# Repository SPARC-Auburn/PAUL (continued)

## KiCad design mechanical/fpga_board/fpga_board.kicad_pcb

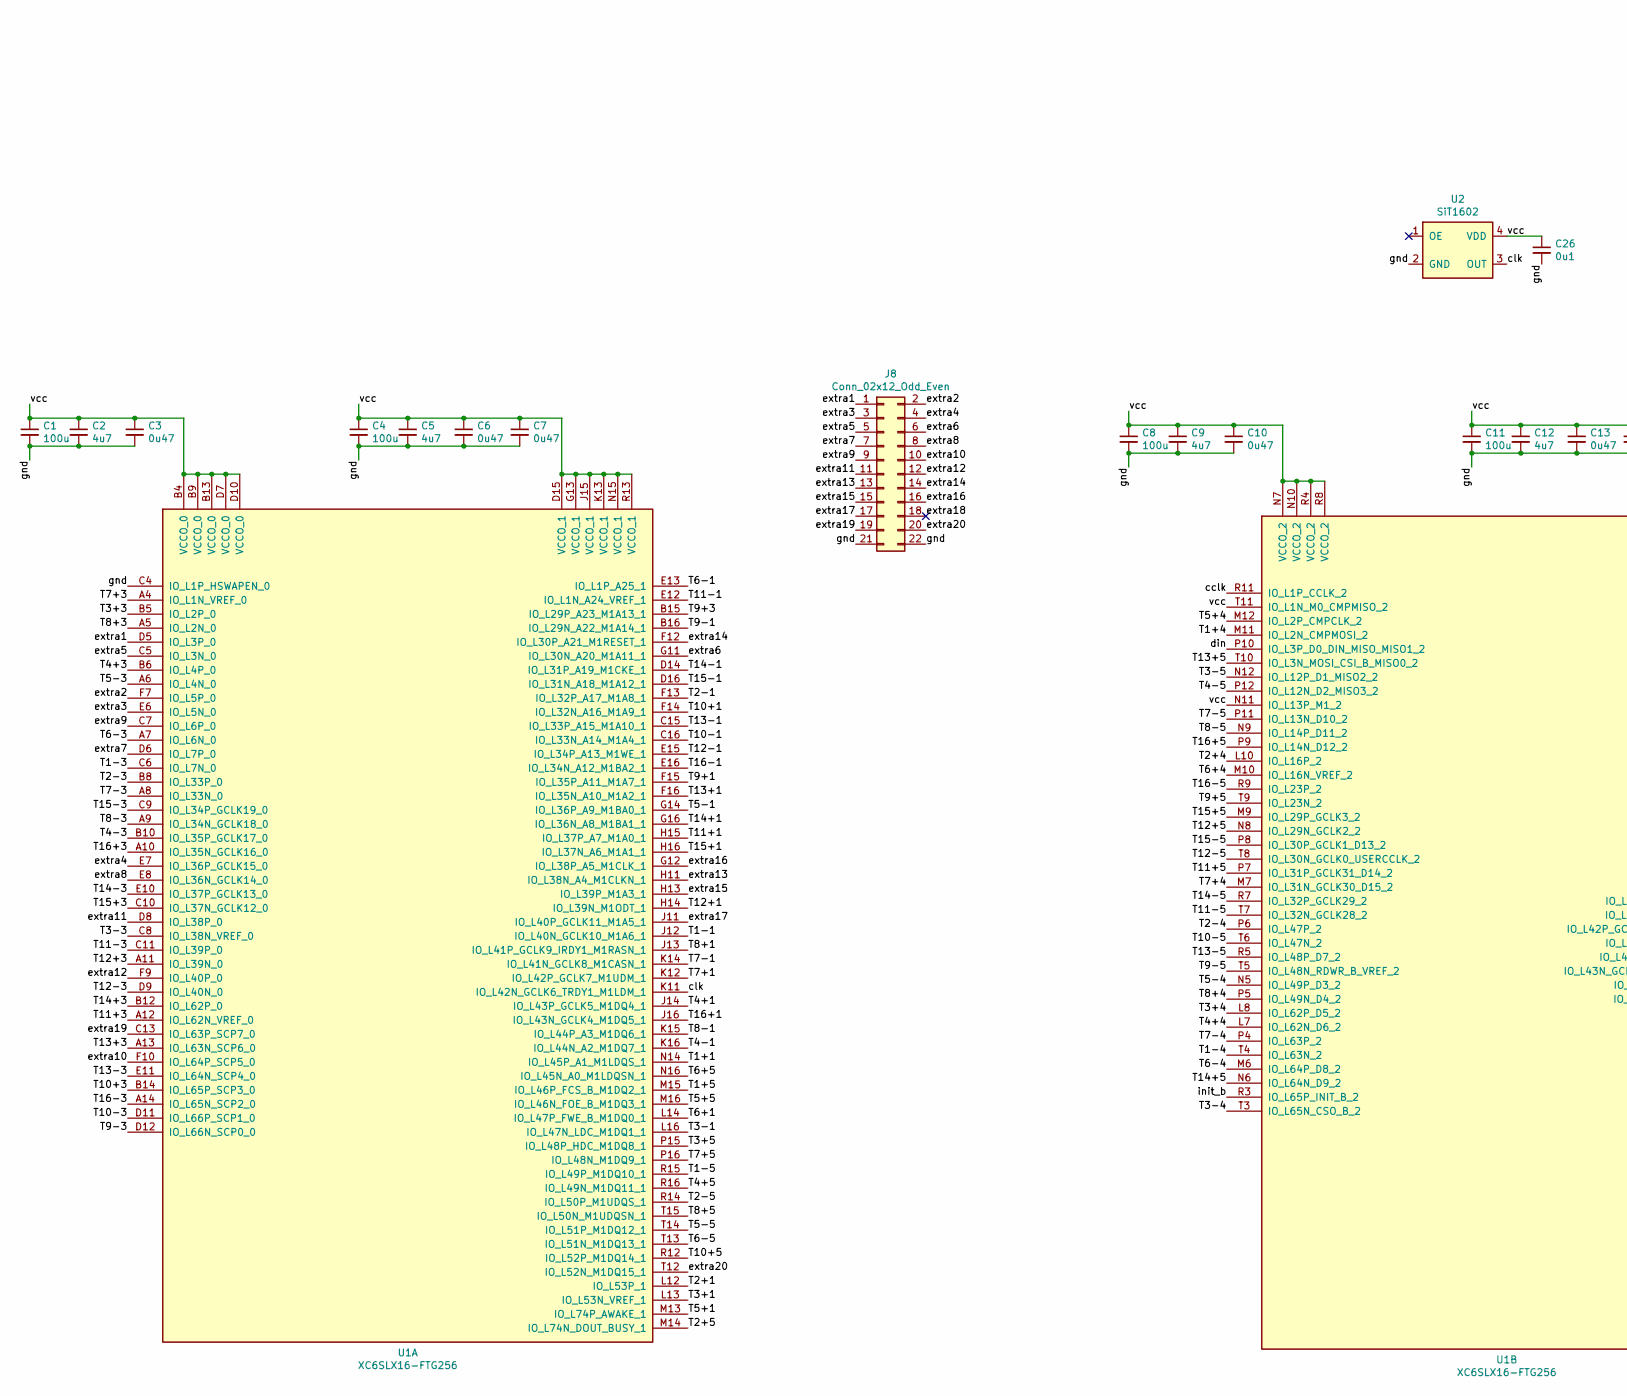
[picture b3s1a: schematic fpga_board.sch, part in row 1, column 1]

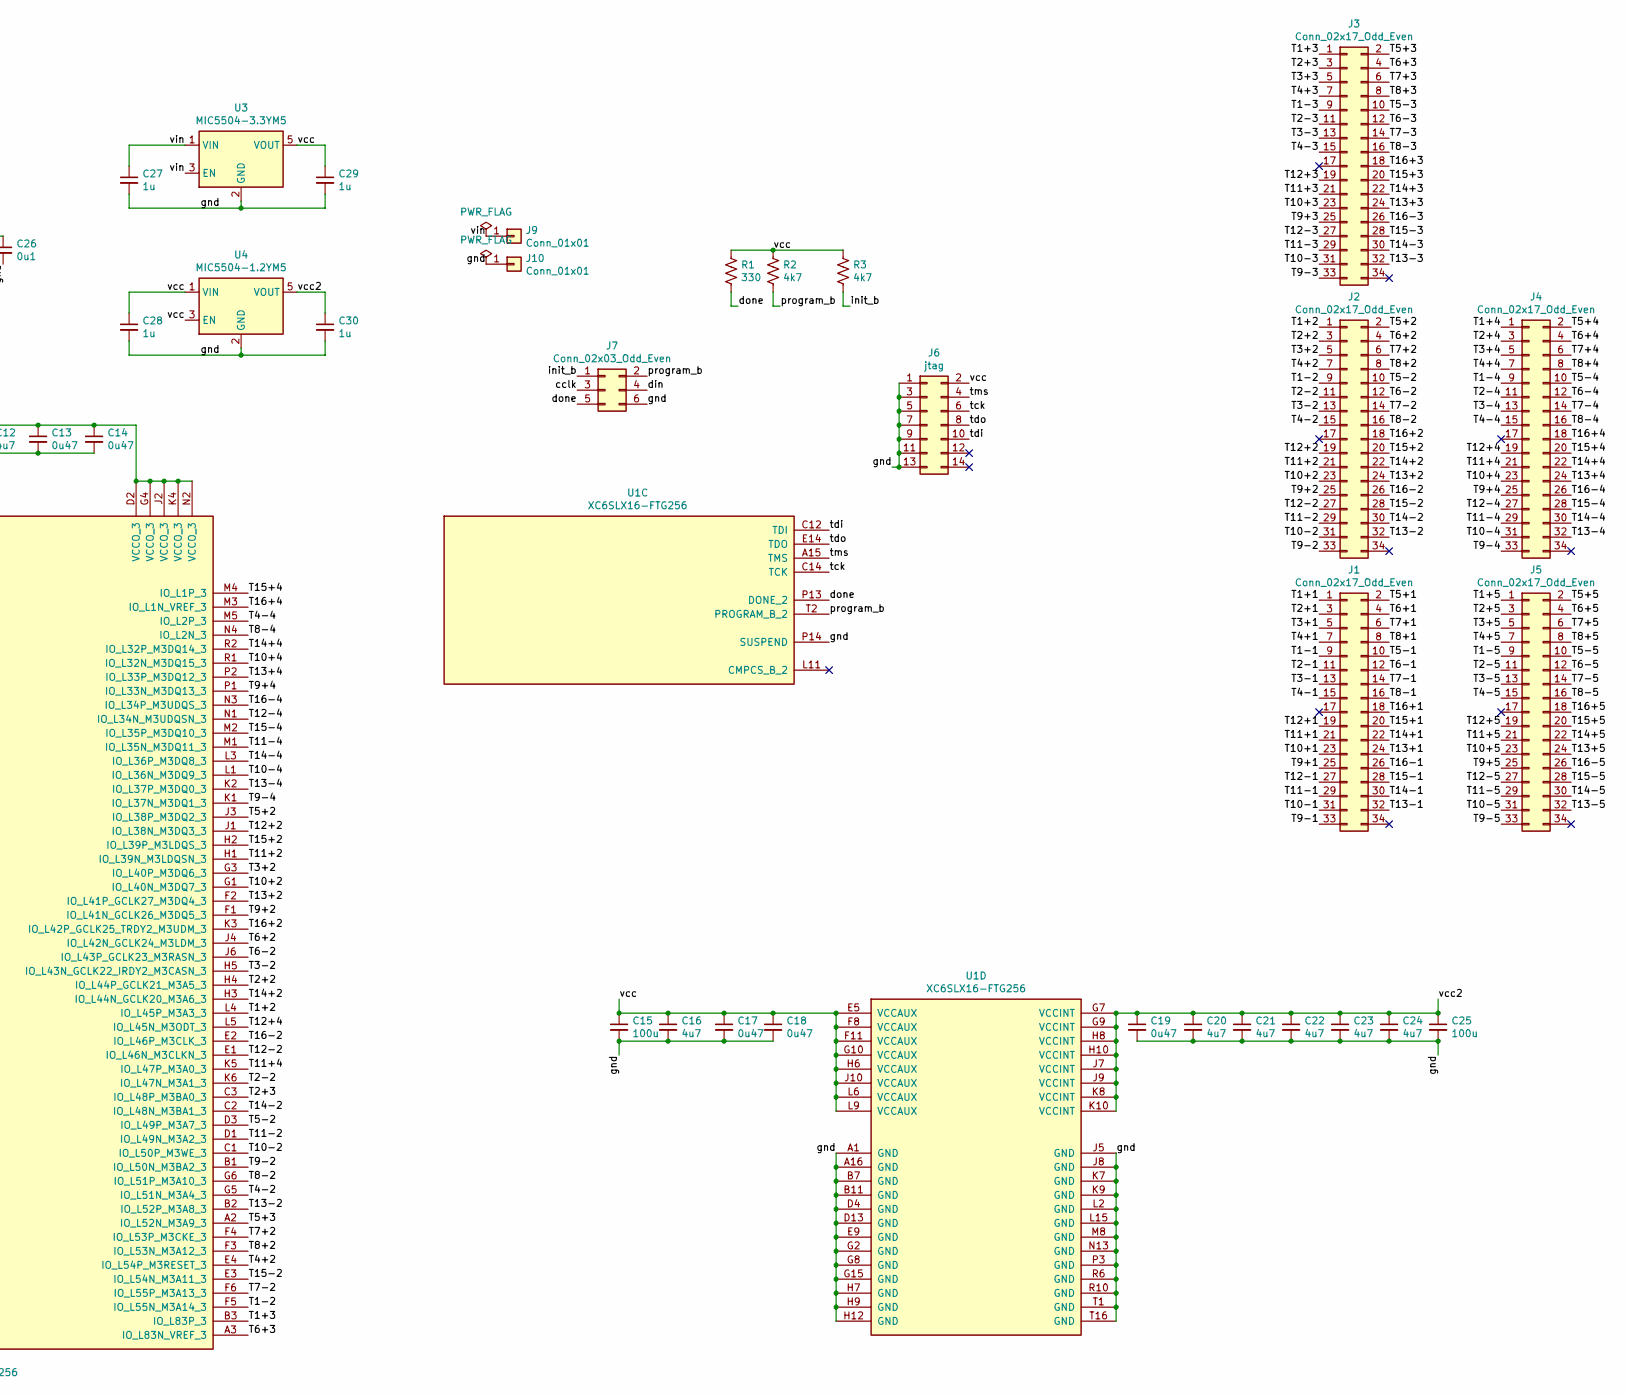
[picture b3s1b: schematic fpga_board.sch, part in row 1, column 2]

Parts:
C1, C4, C8, C11, C15, C25: 100u; C_1210_3225Metric
C2, C5, C9, C12, C16, C20, C21, C22, C23, C24: 4u7; C_0805_2012Metric
C3, C6, C7, C10, C13, C14, C17, C18, C19: 0u47; C_0402_1005Metric
C26: 0u1; C_0402_1005Metric
C27, C28, C29, C30: 1u; C_0603_1608Metric
J1, J2, J3, J4, J5: Conn_02x17_Odd_Even; PinSocket_2x17_P2.54mm_Vertical
J6: jtag; PinSocket_2x07_P2.54mm_Vertical
J7: Conn_02x03_Odd_Even; PinSocket_2x03_P2.54mm_Vertical
J8: Conn_02x12_Odd_Even; PinSocket_2x11_P2.54mm_Vertical
J9, J10: Conn_01x01; Pin_D1.3mm_L11.0mm
R1: 330; R_0603_1608Metric
R2, R3: 4k7; R_0603_1608Metric
U1: XC6SLX16-FTG256; Xilinx_FTG256
U2: SiT1602; SiT1602_7_5
U3: MIC5504-3.3YM5; SOT-23-5
U4: MIC5504-1.2YM5; SOT-23-5

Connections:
/T1+1: J1.1, U1.N14 (IO_L45P_A1_M1LDQS_1)
/T1+2: J2.1, U1.L4 (IO_L45P_M3A3_3)
/T1+3: J3.1, U1.B3 (IO_L83P_3)
/T1+4: J4.1, U1.M11 (IO_L2N_CMPMOSI_2)
/T1+5: J5.1, U1.M15 (IO_L46P_FCS_B_M1DQ2_1)
/T1-1: J1.9, U1.J12 (IO_L40N_GCLK10_M1A6_1)
/T1-2: J2.9, U1.F5 (IO_L55N_M3A14_3)
/T1-3: J3.9, U1.C6 (IO_L7N_0)
/T1-4: J4.9, U1.T4 (IO_L63N_2)
/T1-5: J5.9, U1.R15 (IO_L49P_M1DQ10_1)
/T2+1: J1.3, U1.L12 (IO_L53P_1)
/T2+2: J2.3, U1.H4 (IO_L44P_GCLK21_M3A5_3)
/T2+3: J3.3, U1.C3 (IO_L48P_M3BA0_3)
/T2+4: J4.3, U1.L10 (IO_L16P_2)
/T2+5: J5.3, U1.M14 (IO_L74N_DOUT_BUSY_1)
/T2-1: J1.11, U1.F13 (IO_L32P_A17_M1A8_1)
/T2-2: J2.11, U1.K6 (IO_L47N_M3A1_3)
/T2-3: J3.11, U1.B8 (IO_L33P_0)
/T2-4: J4.11, U1.P6 (IO_L47P_2)
/T2-5: J5.11, U1.R14 (IO_L50P_M1UDQS_1)
/T3+1: J1.5, U1.L13 (IO_L53N_VREF_1)
/T3+2: J2.5, U1.G3 (IO_L40P_M3DQ6_3)
/T3+3: J3.5, U1.B5 (IO_L2P_0)
/T3+4: J4.5, U1.L8 (IO_L62P_D5_2)
/T3+5: J5.5, U1.P15 (IO_L48P_HDC_M1DQ8_1)
/T3-1: J1.13, U1.L16 (IO_L47N_LDC_M1DQ1_1)
/T3-2: J2.13, U1.H5 (IO_L43N_GCLK22_IRDY2_M3CASN_3)
/T3-3: J3.13, U1.C8 (IO_L38N_VREF_0)
/T3-4: J4.13, U1.T3 (IO_L65N_CSO_B_2)
/T3-5: J5.13, U1.N12 (IO_L12P_D1_MISO2_2)
/T4+1: J1.7, U1.J14 (IO_L43P_GCLK5_M1DQ4_1)
/T4+2: J2.7, U1.E4 (IO_L54P_M3RESET_3)
/T4+3: J3.7, U1.B6 (IO_L4P_0)
/T4+4: J4.7, U1.L7 (IO_L62N_D6_2)
/T4+5: J5.7, U1.R16 (IO_L49N_M1DQ11_1)
/T4-1: J1.15, U1.K16 (IO_L44N_A2_M1DQ7_1)
/T4-2: J2.15, U1.G5 (IO_L51N_M3A4_3)
/T4-3: J3.15, U1.B10 (IO_L35P_GCLK17_0)
/T4-4: J4.15, U1.M5 (IO_L2P_3)
/T4-5: J5.15, U1.P12 (IO_L12N_D2_MISO3_2)
/T5+1: J1.2, U1.M13 (IO_L74P_AWAKE_1)
/T5+2: J2.2, U1.J3 (IO_L38P_M3DQ2_3)
/T5+3: J3.2, U1.A2 (IO_L52N_M3A9_3)
/T5+4: J4.2, U1.M12 (IO_L2P_CMPCLK_2)
/T5+5: J5.2, U1.M16 (IO_L46N_FOE_B_M1DQ3_1)
/T5-1: J1.10, U1.G14 (IO_L36P_A9_M1BA0_1)
/T5-2: J2.10, U1.D3 (IO_L49P_M3A7_3)
/T5-3: J3.10, U1.A6 (IO_L4N_0)
/T5-4: J4.10, U1.N5 (IO_L49P_D3_2)
/T5-5: J5.10, U1.T14 (IO_L51P_M1DQ12_1)
/T6+1: J1.4, U1.L14 (IO_L47P_FWE_B_M1DQ0_1)
/T6+2: J2.4, U1.J4 (IO_L42N_GCLK24_M3LDM_3)
/T6+3: J3.4, U1.A3 (IO_L83N_VREF_3)
/T6+4: J4.4, U1.M10 (IO_L16N_VREF_2)
/T6+5: J5.4, U1.N16 (IO_L45N_A0_M1LDQSN_1)
/T6-1: J1.12, U1.E13 (IO_L1P_A25_1)
/T6-2: J2.12, U1.J6 (IO_L43P_GCLK23_M3RASN_3)
/T6-3: J3.12, U1.A7 (IO_L6N_0)
/T6-4: J4.12, U1.M6 (IO_L64P_D8_2)
/T6-5: J5.12, U1.T13 (IO_L51N_M1DQ13_1)
/T7+1: J1.6, U1.K12 (IO_L42P_GCLK7_M1UDM_1)
/T7+2: J2.6, U1.F4 (IO_L53P_M3CKE_3)
/T7+3: J3.6, U1.A4 (IO_L1N_VREF_0)
/T7+4: J4.6, U1.M7 (IO_L31N_GCLK30_D15_2)
/T7+5: J5.6, U1.P16 (IO_L48N_M1DQ9_1)
/T7-1: J1.14, U1.K14 (IO_L41N_GCLK8_M1CASN_1)
/T7-2: J2.14, U1.F6 (IO_L55P_M3A13_3)
/T7-3: J3.14, U1.A8 (IO_L33N_0)
/T7-4: J4.14, U1.P4 (IO_L63P_2)
/T7-5: J5.14, U1.P11 (IO_L13N_D10_2)
/T8+1: J1.8, U1.J13 (IO_L41P_GCLK9_IRDY1_M1RASN_1)
/T8+2: J2.8, U1.F3 (IO_L53N_M3A12_3)
/T8+3: J3.8, U1.A5 (IO_L2N_0)
/T8+4: J4.8, U1.P5 (IO_L49N_D4_2)
/T8+5: J5.8, U1.T15 (IO_L50N_M1UDQSN_1)
/T8-1: J1.16, U1.K15 (IO_L44P_A3_M1DQ6_1)
/T8-2: J2.16, U1.G6 (IO_L51P_M3A10_3)
/T8-3: J3.16, U1.A9 (IO_L34N_GCLK18_0)
/T8-4: J4.16, U1.N4 (IO_L2N_3)
/T8-5: J5.16, U1.N9 (IO_L14P_D11_2)
/T9+1: J1.25, U1.F15 (IO_L35P_A11_M1A7_1)
/T9+2: J2.25, U1.F1 (IO_L41N_GCLK26_M3DQ5_3)
/T9+3: J3.25, U1.B15 (IO_L29P_A23_M1A13_1)
/T9+4: J4.25, U1.P1 (IO_L33N_M3DQ13_3)
/T9+5: J5.25, U1.T9 (IO_L23N_2)
/T9-1: J1.33, U1.B16 (IO_L29N_A22_M1A14_1)
/T9-2: J2.33, U1.B1 (IO_L50N_M3BA2_3)
/T9-3: J3.33, U1.D12 (IO_L66N_SCP0_0)
/T9-4: J4.33, U1.K1 (IO_L37N_M3DQ1_3)
/T9-5: J5.33, U1.T5 (IO_L48N_RDWR_B_VREF_2)
/T10+1: J1.23, U1.F14 (IO_L32N_A16_M1A9_1)
/T10+2: J2.23, U1.G1 (IO_L40N_M3DQ7_3)
/T10+3: J3.23, U1.B14 (IO_L65P_SCP3_0)
/T10+4: J4.23, U1.R1 (IO_L32N_M3DQ15_3)
/T10+5: J5.23, U1.R12 (IO_L52P_M1DQ14_1)
/T10-1: J1.31, U1.C16 (IO_L33N_A14_M1A4_1)
/T10-2: J2.31, U1.C1 (IO_L50P_M3WE_3)
/T10-3: J3.31, U1.D11 (IO_L66P_SCP1_0)
/T10-4: J4.31, U1.L1 (IO_L36N_M3DQ9_3)
/T10-5: J5.31, U1.T6 (IO_L47N_2)
/T11+1: J1.21, U1.H15 (IO_L37P_A7_M1A0_1)
/T11+2: J2.21, U1.H1 (IO_L39N_M3LDQSN_3)
/T11+3: J3.21, U1.A12 (IO_L62N_VREF_0)
/T11+4: J4.21, U1.K5 (IO_L47P_M3A0_3)
/T11+5: J5.21, U1.P7 (IO_L31P_GCLK31_D14_2)
/T11-1: J1.29, U1.E12 (IO_L1N_A24_VREF_1)
/T11-2: J2.29, U1.D1 (IO_L49N_M3A2_3)
/T11-3: J3.29, U1.C11 (IO_L39P_0)
/T11-4: J4.29, U1.M1 (IO_L35N_M3DQ11_3)
/T11-5: J5.29, U1.T7 (IO_L32N_GCLK28_2)
/T12+1: J1.19, U1.H14 (IO_L39N_M1ODT_1)
/T12+2: J2.19, U1.J1 (IO_L38N_M3DQ3_3)
/T12+3: J3.19, U1.A11 (IO_L39N_0)
/T12+4: J4.19, U1.L5 (IO_L45N_M3ODT_3)
/T12+5: J5.19, U1.N8 (IO_L29N_GCLK2_2)
/T12-1: J1.27, U1.E15 (IO_L34P_A13_M1WE_1)
/T12-2: J2.27, U1.E1 (IO_L46N_M3CLKN_3)
/T12-3: J3.27, U1.D9 (IO_L40N_0)
/T12-4: J4.27, U1.N1 (IO_L34N_M3UDQSN_3)
/T12-5: J5.27, U1.T8 (IO_L30N_GCLK0_USERCCLK_2)
/T13+1: J1.24, U1.F16 (IO_L35N_A10_M1A2_1)
/T13+2: J2.24, U1.F2 (IO_L41P_GCLK27_M3DQ4_3)
/T13+3: J3.24, U1.A13 (IO_L63N_SCP6_0)
/T13+4: J4.24, U1.P2 (IO_L33P_M3DQ12_3)
/T13+5: J5.24, U1.T10 (IO_L3N_MOSI_CSI_B_MISO0_2)
/T13-1: J1.32, U1.C15 (IO_L33P_A15_M1A10_1)
/T13-2: J2.32, U1.B2 (IO_L52P_M3A8_3)
/T13-3: J3.32, U1.E11 (IO_L64N_SCP4_0)
/T13-4: J4.32, U1.K2 (IO_L37P_M3DQ0_3)
/T13-5: J5.32, U1.R5 (IO_L48P_D7_2)
/T14+1: J1.22, U1.G16 (IO_L36N_A8_M1BA1_1)
/T14+2: J2.22, U1.H3 (IO_L44N_GCLK20_M3A6_3)
/T14+3: J3.22, U1.B12 (IO_L62P_0)
/T14+4: J4.22, U1.R2 (IO_L32P_M3DQ14_3)
/T14+5: J5.22, U1.N6 (IO_L64N_D9_2)
/T14-1: J1.30, U1.D14 (IO_L31P_A19_M1CKE_1)
/T14-2: J2.30, U1.C2 (IO_L48N_M3BA1_3)
/T14-3: J3.30, U1.E10 (IO_L37P_GCLK13_0)
/T14-4: J4.30, U1.L3 (IO_L36P_M3DQ8_3)
/T14-5: J5.30, U1.R7 (IO_L32P_GCLK29_2)
/T15+1: J1.20, U1.H16 (IO_L37N_A6_M1A1_1)
/T15+2: J2.20, U1.H2 (IO_L39P_M3LDQS_3)
/T15+3: J3.20, U1.C10 (IO_L37N_GCLK12_0)
/T15+4: J4.20, U1.M4 (IO_L1P_3)
/T15+5: J5.20, U1.M9 (IO_L29P_GCLK3_2)
/T15-1: J1.28, U1.D16 (IO_L31N_A18_M1A12_1)
/T15-2: J2.28, U1.E3 (IO_L54N_M3A11_3)
/T15-3: J3.28, U1.C9 (IO_L34P_GCLK19_0)
/T15-4: J4.28, U1.M2 (IO_L35P_M3DQ10_3)
/T15-5: J5.28, U1.P8 (IO_L30P_GCLK1_D13_2)
/T16+1: J1.18, U1.J16 (IO_L43N_GCLK4_M1DQ5_1)
/T16+2: J2.18, U1.K3 (IO_L42P_GCLK25_TRDY2_M3UDM_3)
/T16+3: J3.18, U1.A10 (IO_L35N_GCLK16_0)
/T16+4: J4.18, U1.M3 (IO_L1N_VREF_3)
/T16+5: J5.18, U1.P9 (IO_L14N_D12_2)
/T16-1: J1.26, U1.E16 (IO_L34N_A12_M1BA2_1)
/T16-2: J2.26, U1.E2 (IO_L46P_M3CLK_3)
/T16-3: J3.26, U1.A14 (IO_L65N_SCP2_0)
/T16-4: J4.26, U1.N3 (IO_L34P_M3UDQS_3)
/T16-5: J5.26, U1.R9 (IO_L23P_2)
/cclk: J7.3, U1.R11 (IO_L1P_CCLK_2)
/clk: U1.K11 (IO_L42N_GCLK6_TRDY1_M1LDM_1), U2.3 (OUT)
/din: J7.4, U1.P10 (IO_L3P_D0_DIN_MISO_MISO1_2)
/done: J7.5, R1.2, U1.P13 (DONE_2)
/extra1: J8.1, U1.D5 (IO_L3P_0)
/extra2: J8.2, U1.F7 (IO_L5P_0)
/extra3: J8.3, U1.E6 (IO_L5N_0)
/extra4: J8.4, U1.E7 (IO_L36P_GCLK15_0)
/extra5: J8.5, U1.C5 (IO_L3N_0)
/extra6: J8.6, U1.G11 (IO_L30N_A20_M1A11_1)
/extra7: J8.7, U1.D6 (IO_L7P_0)
/extra8: J8.8, U1.E8 (IO_L36N_GCLK14_0)
/extra9: J8.9, U1.C7 (IO_L6P_0)
/extra10: J8.10, U1.F10 (IO_L64P_SCP5_0)
/extra11: J8.11, U1.D8 (IO_L38P_0)
/extra12: J8.12, U1.F9 (IO_L40P_0)
/extra13: J8.13, U1.H11 (IO_L38N_A4_M1CLKN_1)
/extra14: J8.14, U1.F12 (IO_L30P_A21_M1RESET_1)
/extra15: J8.15, U1.H13 (IO_L39P_M1A3_1)
/extra16: J8.16, U1.G12 (IO_L38P_A5_M1CLK_1)
/extra17: J8.17, U1.J11 (IO_L40P_GCLK11_M1A5_1)
/extra18: J8.18
/extra19: J8.19, U1.C13 (IO_L63P_SCP7_0)
/extra20: J8.20, U1.T12 (IO_L52N_M1DQ15_1)
/gnd: C1.2, C2.2, C3.2, C4.2, C5.2, C6.2, C7.2, C8.2, C9.2, C10.2, C11.2, C12.2, C13.2, C14.2, C15.2, C16.2, C17.2, C18.2, C19.2, C20.2, C21.2, C22.2, C23.2, C24.2, C25.2, C26.2, C27.2, C28.2, C29.2, C30.2, J6.1, J6.3, J6.5, J6.7, J6.9, J6.11, J6.13, J7.6, J8.21, J8.22, J10.1, U1.A1 (GND), U1.A16 (GND), U1.B7 (GND), U1.B11 (GND), U1.C4 (IO_L1P_HSWAPEN_0), U1.D4 (GND), U1.D13 (GND), U1.E9 (GND), U1.G2 (GND), U1.G8 (GND), U1.G15 (GND), U1.H7 (GND), U1.H9 (GND), U1.H12 (GND), U1.J5 (GND), U1.J8 (GND), U1.K7 (GND), U1.K9 (GND), U1.L2 (GND), U1.L15 (GND), U1.M8 (GND), U1.N13 (GND), U1.P3 (GND), U1.P14 (SUSPEND), U1.R6 (GND), U1.R10 (GND), U1.T1 (GND), U1.T16 (GND), U2.2 (GND), U3.2 (GND), U4.2 (GND)
/init_b: J7.1, R3.2, U1.R3 (IO_L65P_INIT_B_2)
/program_b: J7.2, R2.2, U1.T2 (PROGRAM_B_2)
/tck: J6.6, U1.C14 (TCK)
/tdi: J6.10, U1.C12 (TDI)
/tdo: J6.8, U1.E14 (TDO)
/tms: J6.4, U1.A15 (TMS)
/vcc: C1.1, C2.1, C3.1, C4.1, C5.1, C6.1, C7.1, C8.1, C9.1, C10.1, C11.1, C12.1, C13.1, C14.1, C15.1, C16.1, C17.1, C18.1, C26.1, C28.1, C29.1, J6.2, R1.1, R2.1, R3.1, U1.B4 (VCCO_0), U1.B9 (VCCO_0), U1.B13 (VCCO_0), U1.D2 (VCCO_3), U1.D7 (VCCO_0), U1.D10 (VCCO_0), U1.D15 (VCCO_1), U1.E5 (VCCAUX), U1.F8 (VCCAUX), U1.F11 (VCCAUX), U1.G4 (VCCO_3), U1.G10 (VCCAUX), U1.G13 (VCCO_1), U1.H6 (VCCAUX), U1.J2 (VCCO_3), U1.J10 (VCCAUX), U1.J15 (VCCO_1), U1.K4 (VCCO_3), U1.K13 (VCCO_1), U1.L6 (VCCAUX), U1.L9 (VCCAUX), U1.N2 (VCCO_3), U1.N7 (VCCO_2), U1.N10 (VCCO_2), U1.N11 (IO_L13P_M1_2), U1.N15 (VCCO_1), U1.R4 (VCCO_2), U1.R8 (VCCO_2), U1.R13 (VCCO_1), U1.T11 (IO_L1N_M0_CMPMISO_2), U2.4 (VDD), U3.5 (VOUT), U4.1 (VIN), U4.3 (EN)
/vcc2: C19.1, C20.1, C21.1, C22.1, C23.1, C24.1, C25.1, C30.1, U1.G7 (VCCINT), U1.G9 (VCCINT), U1.H8 (VCCINT), U1.H10 (VCCINT), U1.J7 (VCCINT), U1.J9 (VCCINT), U1.K8 (VCCINT), U1.K10 (VCCINT), U4.5 (VOUT)
/vin: C27.1, J9.1, U3.1 (VIN), U3.3 (EN)

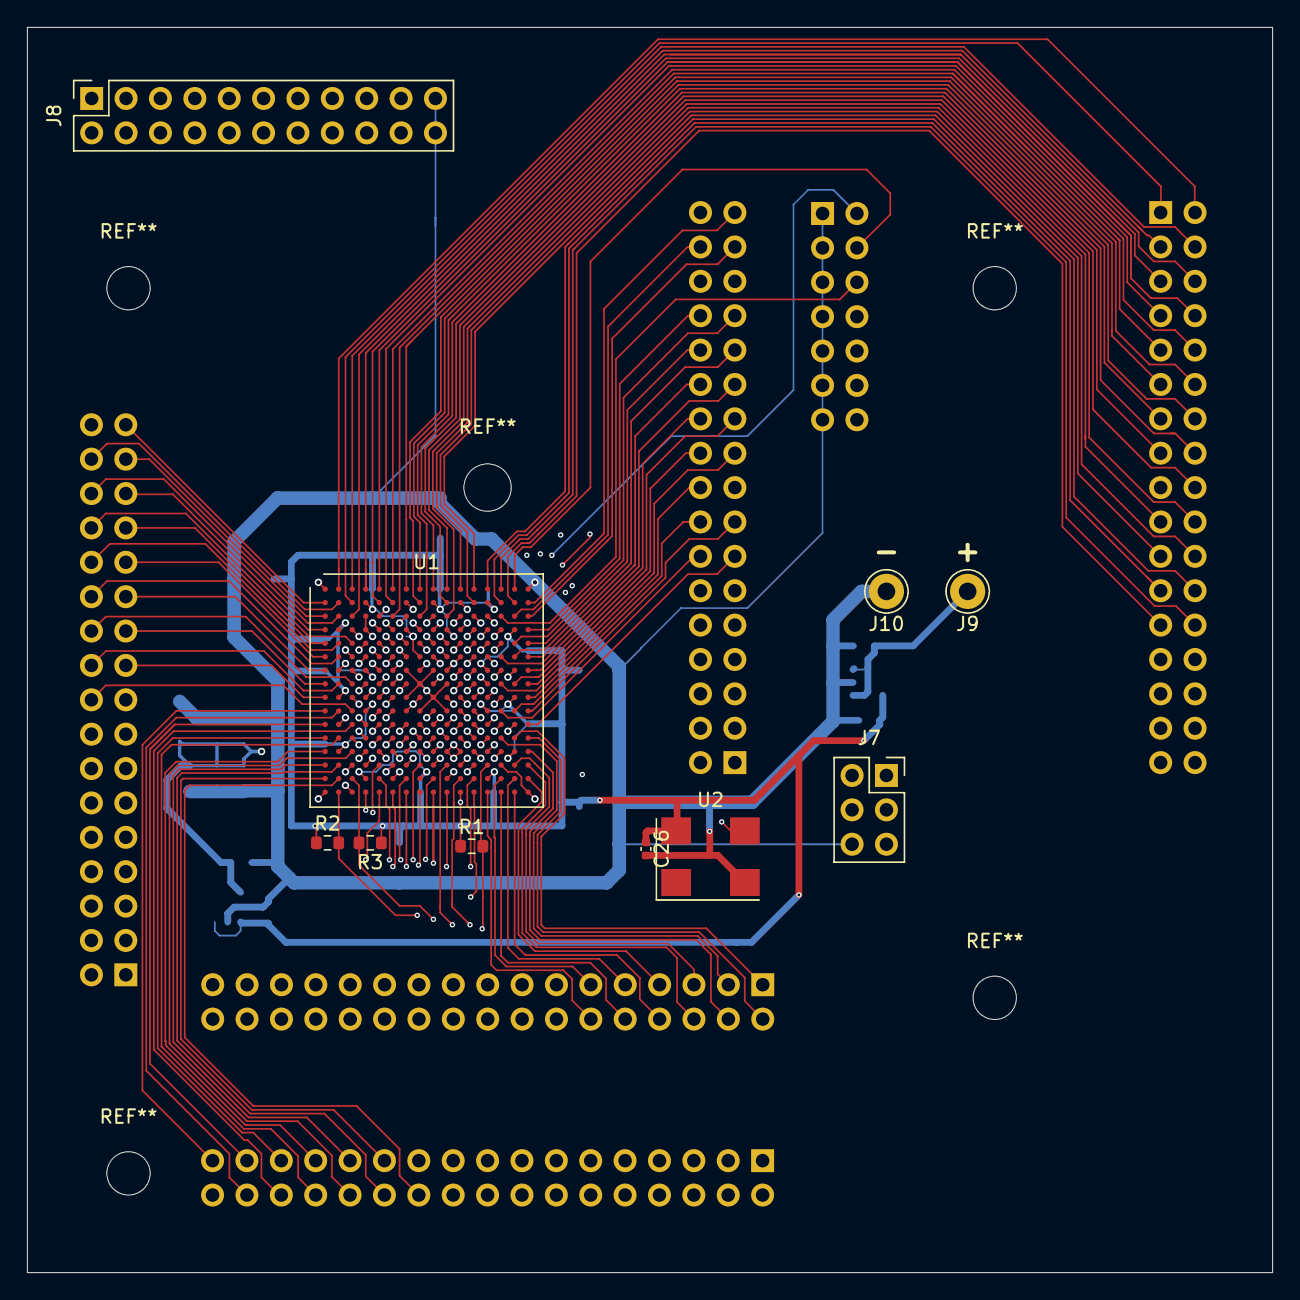
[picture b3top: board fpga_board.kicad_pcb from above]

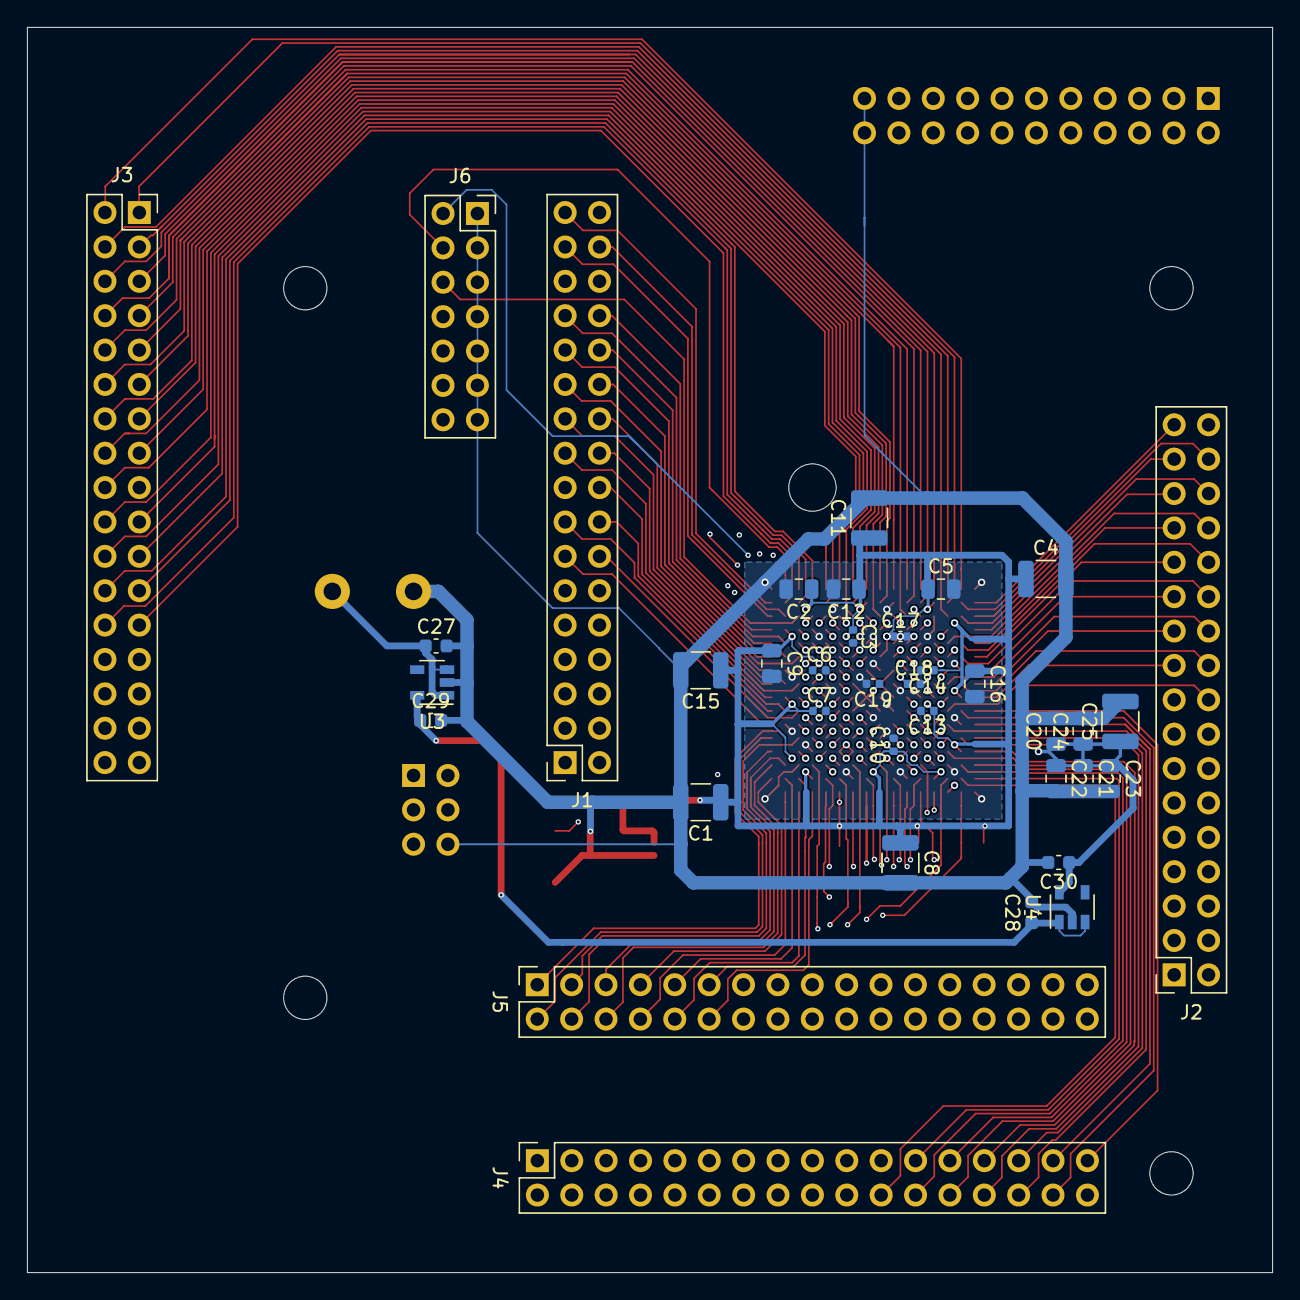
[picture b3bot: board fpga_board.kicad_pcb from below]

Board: 4 copper layers, 92.0 x 92.0 mm, 47 parts (37 on the bottom side), 193 nets.

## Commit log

2020-10-25 Initial VHDL commit
2020-10-30 Added simulation code
2020-10-31 Small improvements
    Corrected density value, accounted for negative magnitude
2021-02-10 Added transducer board (incomplete)
2021-02-22 Completed transducer board layout
2021-03-02 Transducer board update
    Flipped front and back, added ground plane, and thickened bypass cap traces
2021-03-17 Transducers are driven with a bipolar waveform
2021-03-17 fpga board initial commit, not done yet
2021-03-17 Decreased transducer hole size
    Also adjusted gnd plane slightly
2021-03-19 all fpga pins routed, still need regulators
2021-03-20 constraint file extractor
2021-03-24 pwm top improved for 160 outputs
2021-03-29 Added VHDL features and reorganized
    Also added another constraints file and a description of clk wizard settings
2021-03-29 Constraint generator writes to a file
2021-03-30 Tightened transducer board mounting hole size
2021-03-31 Moved FPGA and added hole
2021-04-07 Added mounting holes, reduced size on FPGA board
2021-04-09 Clearly mark which power wire goes where
2021-04-10 Added linear regulators and oscillator
2021-04-10 Shortened some traces
2021-04-12 increased trace thickness on transducer board
2021-04-13 drc fixes
2021-06-26 Renamed mechanical folder to electrical
2021-09-02 Tweaks to PCBs
2021-10-14 Adding the initial desgin of the buffer board and the PLL generated to replace the clock_wizard.
2021-10-17 Switched to FPGA on transducer board
2021-10-21 Set VHDL to 16 outputs
2022-01-27 Add Arduino test program
2022-02-13 Switched to MachXO3 FPGA
    Also switched to Kicad 6
2022-03-31 Fixed XL62083 pins and made other adjustments
2022-04-02 Swapped some parts
2022-04-14 Add a few components
2022-04-14 Adjustments for final file generation
